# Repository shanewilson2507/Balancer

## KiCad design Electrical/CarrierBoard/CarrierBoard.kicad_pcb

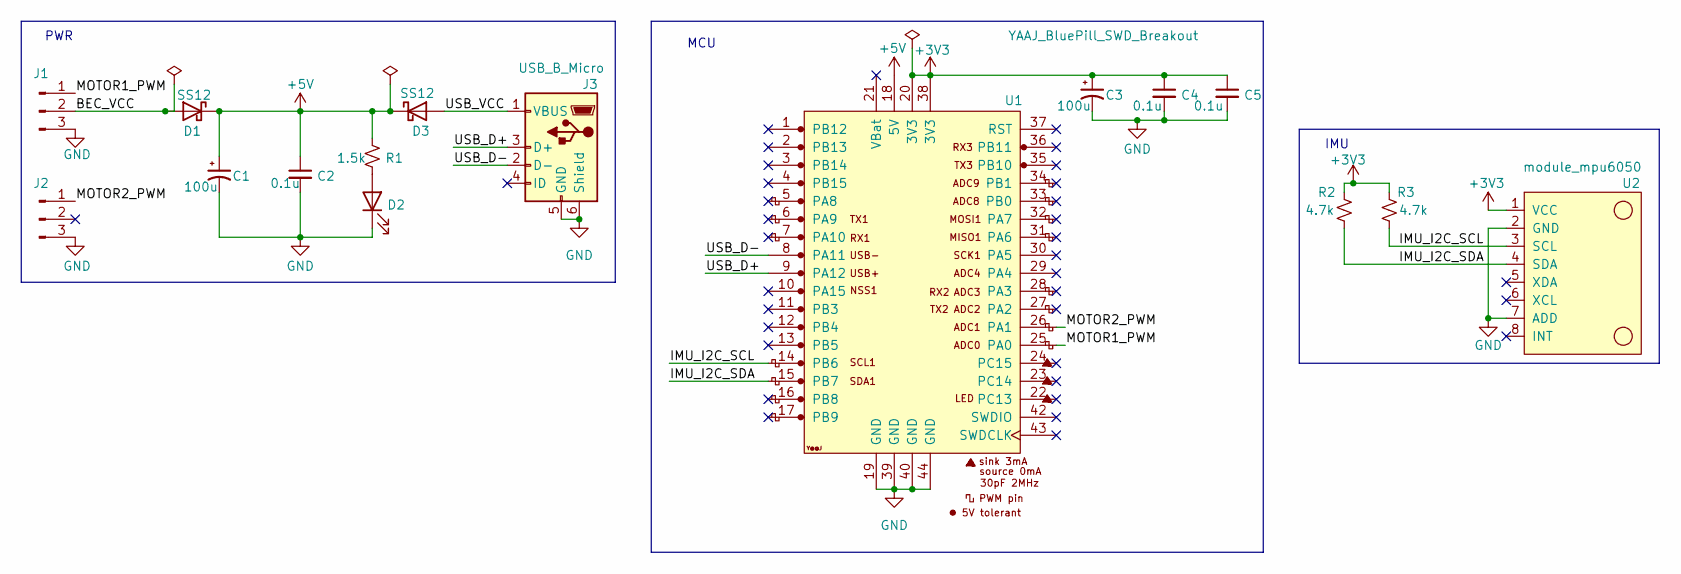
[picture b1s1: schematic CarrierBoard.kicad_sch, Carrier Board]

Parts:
C1, C3: 100u; C_Radial_D6.3mm_H11.0mm_P2.50mm; digikey 1189-2260-ND
C2, C4, C5: 0.1u; C_0805_2012Metric_Pad1.18x1.45mm_HandSolder; digikey 399-C0805C104K5RACTUCT-ND
D1, D3: SS12; D_SMA_Handsoldering; digikey 1801-SS12CT-ND
D2: LED; LED_PLCC-2_3x2mm_KA; digikey CLM3C-AKW-CUBVA353CT-ND
J1, J2: Conn_01x03_Pin; PinHeader_1x03_P2.54mm_Vertical
J3: USB_B_Micro; USB_Micro-B_Amphenol_10118193-0001LF_Horizontal; digikey 609-4616-1-ND
R1: 1.5k; R_0805_2012Metric_Pad1.20x1.40mm_HandSolder; digikey 541-4161-1-ND
R2, R3: 4.7k; R_0805_2012Metric_Pad1.20x1.40mm_HandSolder; digikey 541-4131-1-ND
U1: YAAJ_BluePill_SWD_Breakout; YAAJ_BluePill_SWD_2
U2: module_mpu6050

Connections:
+3V3: C3.1, C4.1, C5.1, R2.1, R3.1, U1.20 (3V3), U1.38 (3V3), U2.1 (VCC)
+5V: C1.1, C2.1, D1.1 (K), D3.1 (K), R1.1, U1.18 (5V)
/BEC_VCC: D1.2 (A), J1.2
/IMU_I2C_SCL: R3.2, U1.14 (PB6), U2.3 (SCL)
/IMU_I2C_SDA: R2.2, U1.15 (PB7), U2.4 (SDA)
/MOTOR1_PWM: J1.1, U1.25 (PA0)
/MOTOR2_PWM: J2.1, U1.26 (PA1)
/USB_D+: J3.3 (D+), U1.9 (PA12)
/USB_D-: J3.2 (D-), U1.8 (PA11)
/USB_VCC: D3.2 (A), J3.1 (VBUS)
GND: C1.2, C2.2, C3.2, C4.2, C5.2, D2.1 (K), J1.3, J2.3, J3.5 (GND), J3.6 (Shield), U1.19 (GND), U1.39 (GND), U1.40 (GND), U1.44 (GND), U2.2 (GND), U2.7 (ADD)
unnamed: D2.2 (A), R1.2

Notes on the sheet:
IMU
PWR
MCU

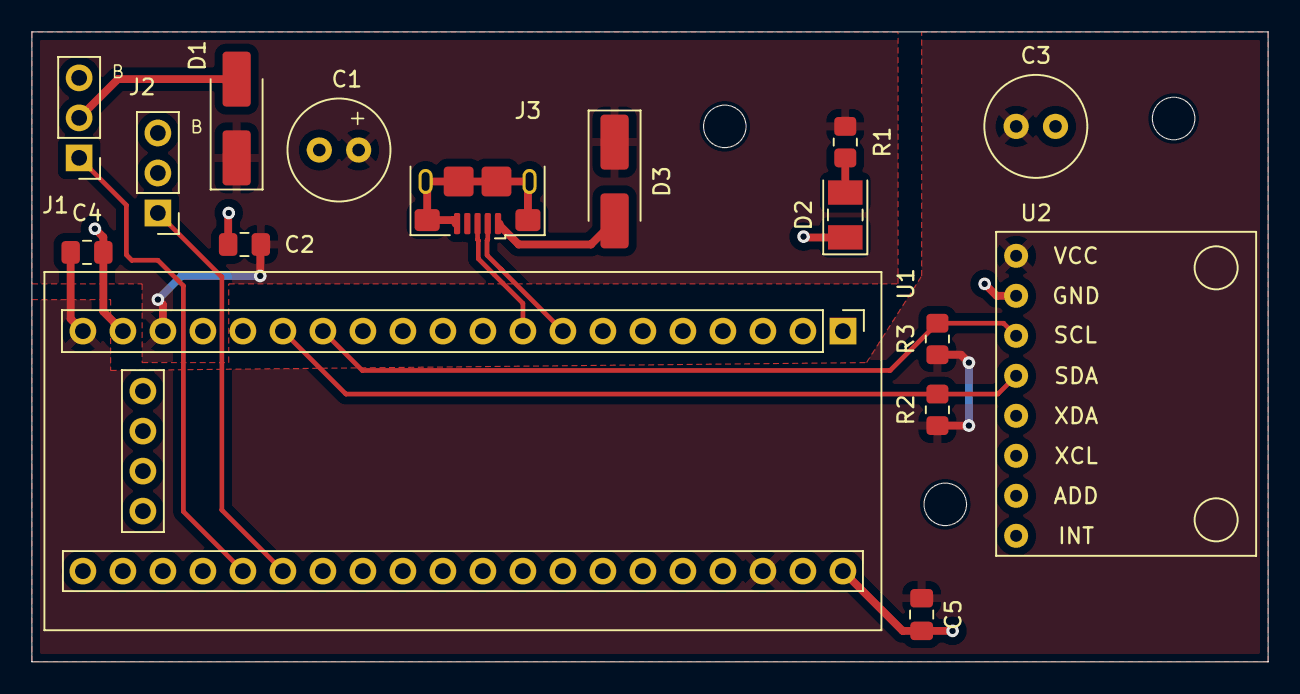
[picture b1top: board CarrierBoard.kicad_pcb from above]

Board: 2 copper layers, 78.5 x 40.0 mm, 16 parts (0 on the bottom side), 12 nets.

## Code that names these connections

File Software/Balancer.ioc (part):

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Mcu.Name=STM32F103C(8-B)Tx
Mcu.Package=LQFP48
Mcu.UserName=STM32F103C8Tx
PA0-WKUP.GPIOParameters=GPIO_Label
PA0-WKUP.GPIO_Label=MOTOR1_PWM
PA0-WKUP.Signal=S_TIM2_CH1_ETR
PA1.GPIOParameters=GPIO_Label
PA1.GPIO_Label=MOTOR2_PWM
PA1.Signal=S_TIM2_CH2
PA11.Mode=Device
PA11.Signal=USB_DM
PA12.Mode=Device
PA12.Signal=USB_DP
PA13.Mode=Serial_Wire
PA13.Signal=SYS_JTMS-SWDIO
PA14.Mode=Serial_Wire
PA14.Signal=SYS_JTCK-SWCLK
PB6.GPIOParameters=GPIO_Label
PB6.GPIO_Label=IMU_I2C_SCL
PB6.Mode=I2C
PB6.Signal=I2C1_SCL
PB7.GPIOParameters=GPIO_Label
PB7.GPIO_Label=IMU_I2C_SDA
PB7.Mode=I2C
PB7.Signal=I2C1_SDA
PC13-TAMPER-RTC.GPIOParameters=GPIO_Label
PC13-TAMPER-RTC.GPIO_Label=LED_ONBOARD
PC13-TAMPER-RTC.Signal=GPIO_Output
PD0-OSC_IN.Mode=HSE-External-Oscillator
PD0-OSC_IN.Signal=RCC_OSC_IN
PD1-OSC_OUT.Mode=HSE-External-Oscillator
PD1-OSC_OUT.Signal=RCC_OSC_OUT
RCC.SYSCLKFreq_VALUE=48000000
RCC.SYSCLKSource=RCC_SYSCLKSOURCE_PLLCLK
board=custom

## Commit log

2026-04-19 Initial monorepo setup for Balancer system, contining Software, Electrical, Mechanical and Control subfolders
2026-05-06 Control: add trim point identification workflow and firmware support
    - Add raw step test data and plotting script for trim estimation
    - Implement TrimIdentificationApp for data collection
    - Add IMU calibration routine on startup
    - Update App and SystemIdentification components
2026-05-10 Software: Restructure firmware architecture into layered HAL-based system
    - Introduced App/Apps separation for multiple application entry points
    - Reorganised Middleware into functional modules:
    Devices, Control, Communication, Services, Observers, Math
    - Introduced PlatformInterface abstraction layer
    - Implemented compile-time platform selection (TARGET_PLATFORM)
    - Refactored CMake dependency graph to match layered architecture
2026-05-13 Software: Implement SystemIdentificationApp with multi-rate control architecture
    - Add PI stabilizer for balancing
    - Add complementary filter for state estimation
    - Add PRBS excitation generator for system ID
    - Introduce time-based scheduling flags (1 kHz base tick)
    - Replace task-specific flags with rate-based scheduling architecture
